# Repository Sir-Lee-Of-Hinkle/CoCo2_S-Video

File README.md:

I've tested these boards. They work but the colors are off.

I use an S-Video to Composite adapter from that jungle website if I need artifact colors.

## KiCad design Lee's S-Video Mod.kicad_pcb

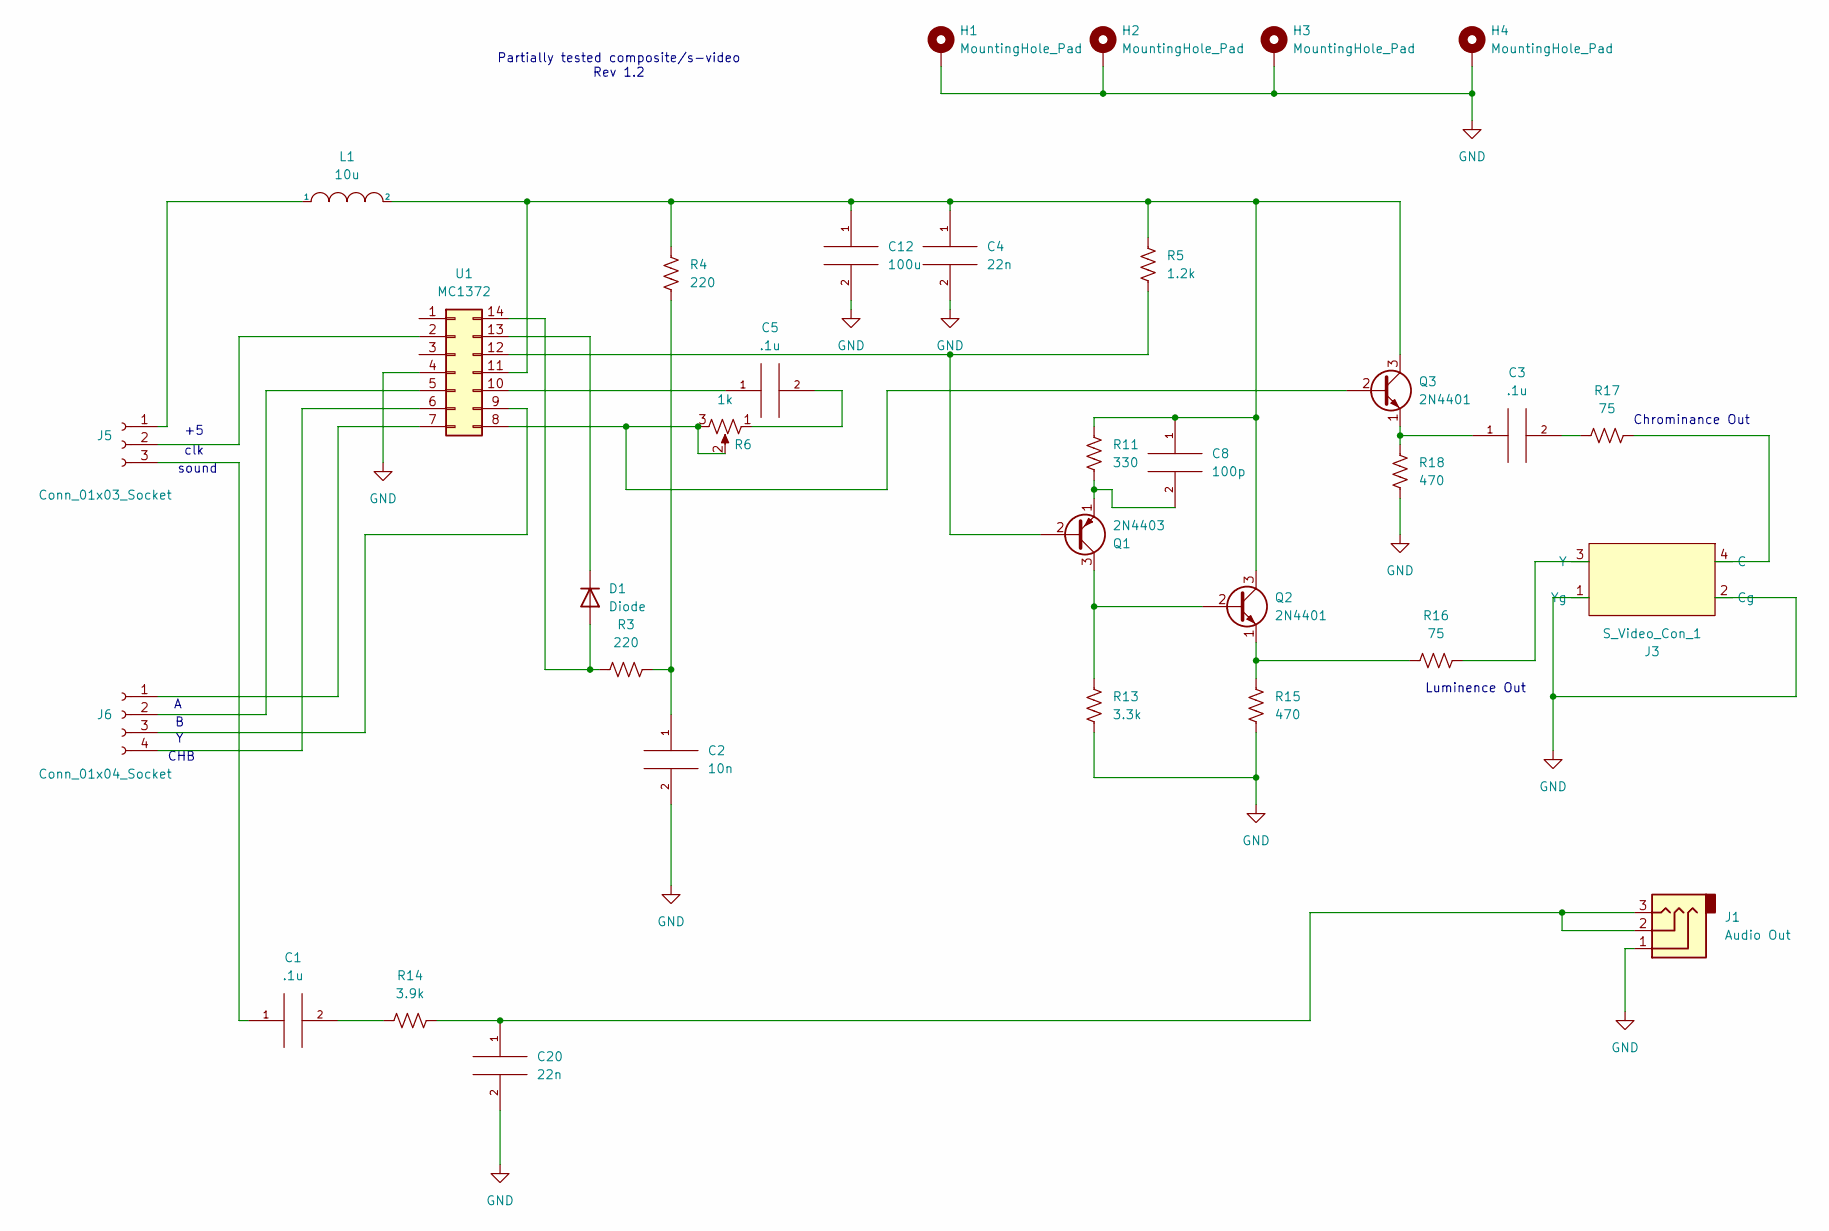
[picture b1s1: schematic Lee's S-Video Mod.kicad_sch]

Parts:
C1, C3, C5: .1u; C_Disc_D4.3mm_W1.9mm_P5.00mm
C2: 10n; C_Disc_D4.3mm_W1.9mm_P5.00mm
C4, C20: 22n; C_Disc_D4.3mm_W1.9mm_P5.00mm
C8: 100p; C_Disc_D4.3mm_W1.9mm_P5.00mm
C12: 100u; CP_Radial_D5.0mm_P2.50mm
D1: Diode; D_5W_P5.08mm_Vertical_KathodeUp
H1, H2, H3, H4: MountingHole_Pad; Mounting_Hole_050
J1: Audio Out; 125_Audio_Jack
J3: S_Video_Con_1; S_Video_PCB
J5: Conn_01x03_Socket; Connector_01x03_2.54_Vertical
J6: Conn_01x04_Socket; Connector_01_04_2.54_Vertical
L1: 10u; R_Axial_DIN0309_L9.0mm_D3.2mm_P5.08mm_Vertical
Q1: 2N4403; TO-92_Inline_Wide
Q2, Q3: 2N4401; TO-92_Inline_Wide
R3, R4: 220; R_Axial_DIN0309_L9.0mm_D3.2mm_P5.08mm_Vertical
R5: 1.2k; R_Axial_DIN0309_L9.0mm_D3.2mm_P5.08mm_Vertical
R6: 1k; Potentiometer_Vertical_2.54_Inline
R11: 330; R_Axial_DIN0309_L9.0mm_D3.2mm_P5.08mm_Vertical
R13: 3.3k; R_Axial_DIN0309_L9.0mm_D3.2mm_P5.08mm_Vertical
R14: 3.9k; R_Axial_DIN0309_L9.0mm_D3.2mm_P5.08mm_Vertical
R15, R18: 470; R_Axial_DIN0309_L9.0mm_D3.2mm_P5.08mm_Vertical
R16, R17: 75; R_Axial_DIN0309_L9.0mm_D3.2mm_P5.08mm_Vertical
U1: MC1372; DIP-14_W7.62mm_Socket

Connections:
GND: C2.2, C4.2, C12.2, C20.2, H1.1, H2.1, H3.1, H4.1, J1.1, J3.1 (Yg), J3.2 (Cg), R13.2, R15.2, R18.2, U1.4
unnamed: C1.2, R14.1
unnamed: C2.1, R3.1, R4.2
unnamed: C3.2, R17.1
unnamed: C5.2, R6.1
unnamed: C20.1, J1.2, J1.3, R14.2
unnamed: D1.2 (A), R3.2, U1.14
unnamed: D1.1 (K), U1.13
unnamed: J3.4 (C), R17.2
unnamed: J3.3 (Y), R16.2
unnamed: J5.1, L1.1
unnamed: J5.2, U1.2
unnamed: C1.1, J5.3
unnamed: J6.1, U1.7
unnamed: J6.2, U1.5
unnamed: J6.3, U1.9
unnamed: J6.4, U1.6
unnamed: Q1.2 (B), R5.2, U1.12
unnamed: Q1.3 (C), Q2.2 (B), R13.1
unnamed: C8.2, Q1.1 (E), R11.2
unnamed: C4.1, C8.1, C12.1, L1.2, Q2.3 (C), Q3.3 (C), R4.1, R5.1, R11.1, U1.11
unnamed: Q2.1 (E), R15.1, R16.1
unnamed: Q3.2 (B), R6.2, R6.3, U1.8
unnamed: C3.1, Q3.1 (E), R18.1
unnamed: C5.1, U1.10

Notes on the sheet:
clk
sound
CHB
Chrominance Out
Luminence Out
Partially tested composite/s-video Rev 1.2

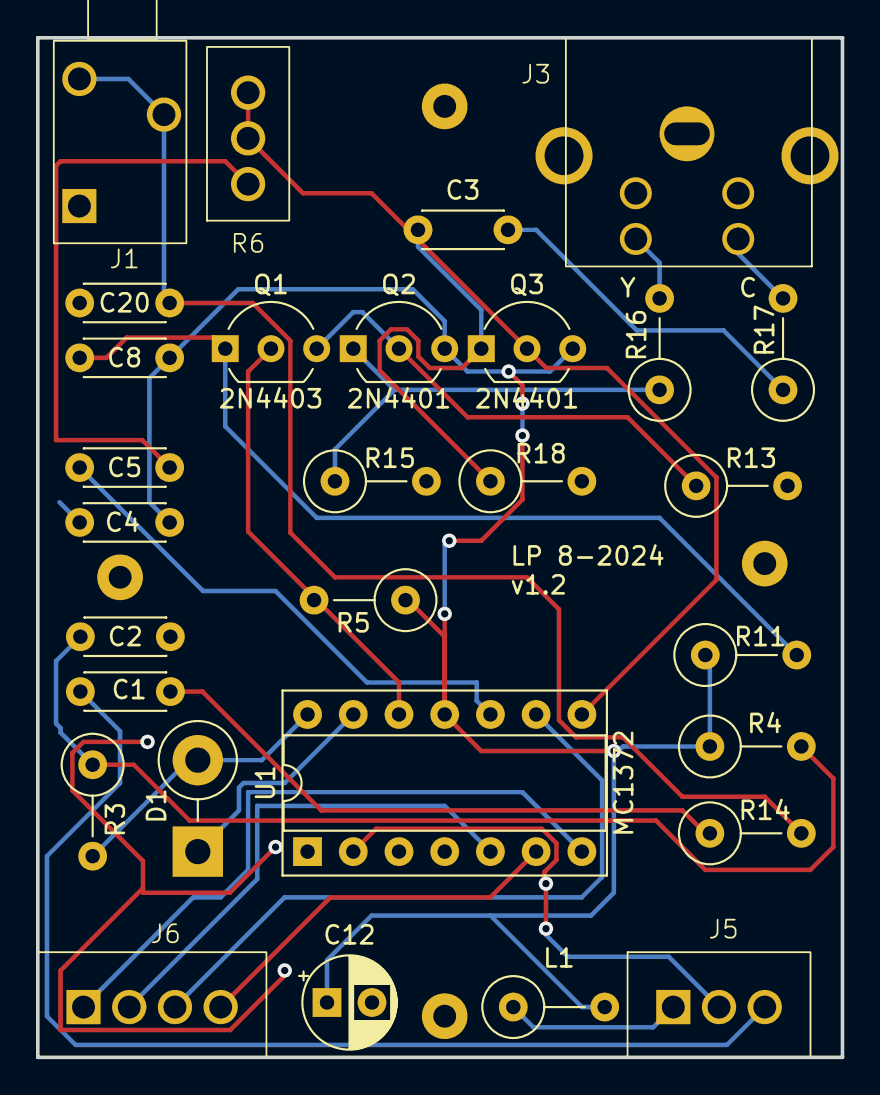
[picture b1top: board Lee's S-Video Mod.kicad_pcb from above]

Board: 2 copper layers, 44.7 x 56.6 mm, 33 parts (0 on the bottom side), 25 nets.

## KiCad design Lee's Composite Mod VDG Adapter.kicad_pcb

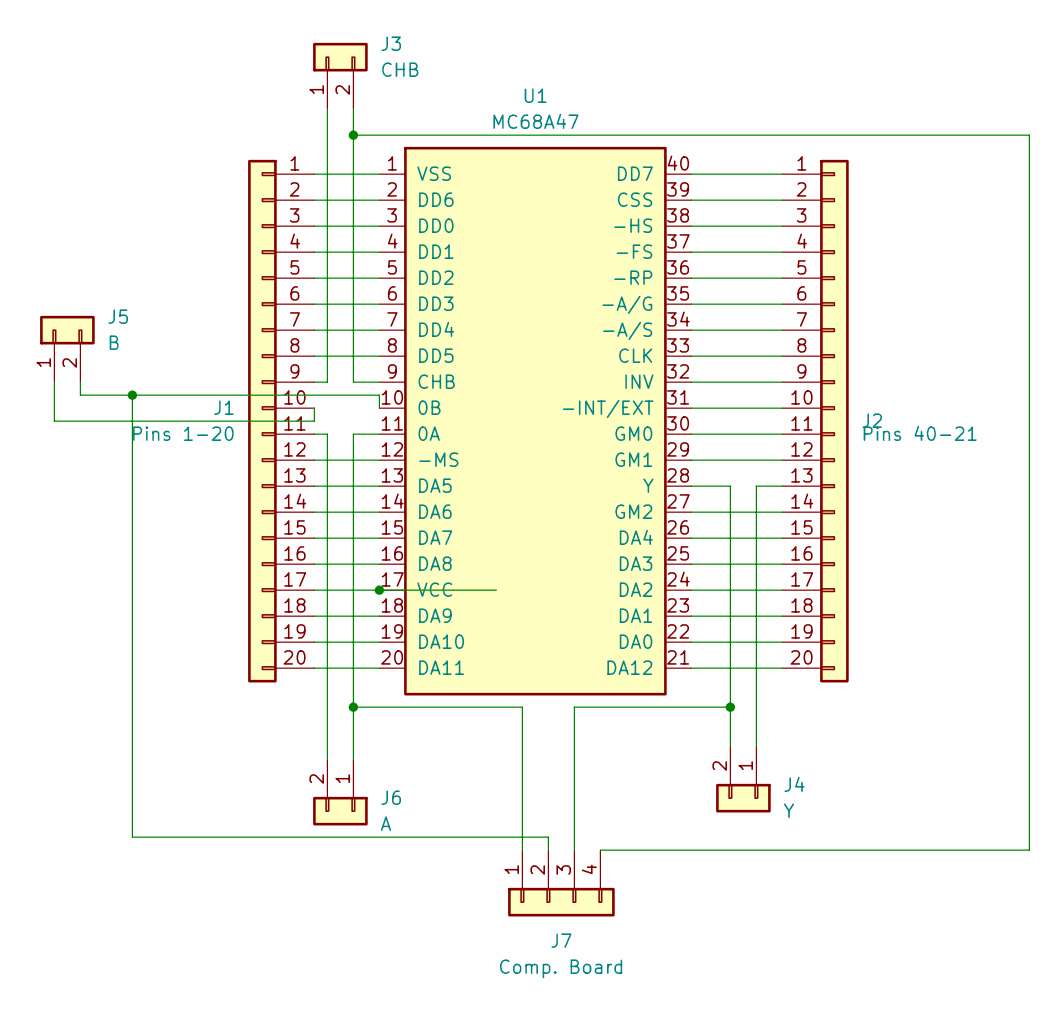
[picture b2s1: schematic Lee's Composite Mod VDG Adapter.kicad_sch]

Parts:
J1: Pins 1-20; PinHeader_1x20_P2.54mm_Vertical
J2: Pins 40-21; PinHeader_1x20_P2.54mm_Vertical
J3: CHB; PinHeader_1x02_P2.54mm_Vertical
J4: Y; PinHeader_1x02_P2.54mm_Vertical
J5: B; PinHeader_1x02_P2.54mm_Vertical
J6: A; PinHeader_1x02_P2.54mm_Vertical
J7: Comp. Board; PinHeader_1x04_P2.54mm_Vertical
U1: MC68A47; DIP-40_W15.24mm

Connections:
unnamed: J1.1, U1.1 (VSS)
unnamed: J1.2, U1.2 (DD6)
unnamed: J1.3, U1.3 (DD0)
unnamed: J1.4, U1.4 (DD1)
unnamed: J1.5, U1.5 (DD2)
unnamed: J1.6, U1.6 (DD3)
unnamed: J1.7, U1.7 (DD4)
unnamed: J1.8, U1.8 (DD5)
unnamed: J1.9, J3.1
unnamed: J1.10, J5.1
unnamed: J1.11, J6.2
unnamed: J1.12, U1.12 (-MS)
unnamed: J1.13, U1.13 (DA5)
unnamed: J1.14, U1.14 (DA6)
unnamed: J1.15, U1.15 (DA7)
unnamed: J1.16, U1.16 (DA8)
unnamed: J1.17, U1.17 (VCC)
unnamed: J1.18, U1.18 (DA9)
unnamed: J1.19, U1.19 (DA10)
unnamed: J1.20, U1.20 (DA11)
unnamed: J2.1, U1.40 (DD7)
unnamed: J2.2, U1.39 (CSS)
unnamed: J2.3, U1.38 (-HS)
unnamed: J2.4, U1.37 (-FS)
unnamed: J2.5, U1.36 (-RP)
unnamed: J2.6, U1.35 (-A/G)
unnamed: J2.7, U1.34 (-A/S)
unnamed: J2.8, U1.33 (CLK)
unnamed: J2.9, U1.32 (INV)
unnamed: J2.10, U1.31 (-INT/EXT)
unnamed: J2.11, U1.30 (GM0)
unnamed: J2.12, U1.29 (GM1)
unnamed: J2.13, J4.1
unnamed: J2.14, U1.27 (GM2)
unnamed: J2.15, U1.26 (DA4)
unnamed: J2.16, U1.25 (DA3)
unnamed: J2.17, U1.24 (DA2)
unnamed: J2.18, U1.23 (DA1)
unnamed: J2.19, U1.22 (DA0)
unnamed: J2.20, U1.21 (DA12)
unnamed: J3.2, J7.4, U1.9 (CHB)
unnamed: J4.2, J7.3, U1.28 (Y)
unnamed: J5.2, J7.2, U1.10 (0B)
unnamed: J6.1, J7.1, U1.11 (0A)

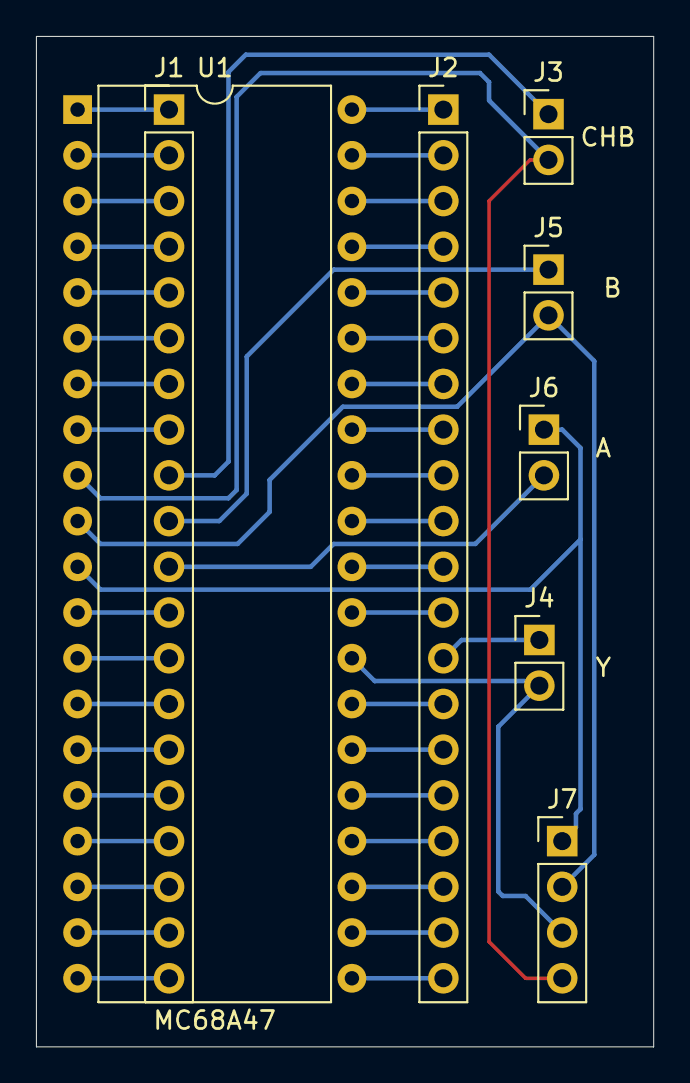
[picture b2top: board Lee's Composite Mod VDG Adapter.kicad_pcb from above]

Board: 2 copper layers, 34.3 x 56.1 mm, 8 parts (0 on the bottom side), 44 nets.
